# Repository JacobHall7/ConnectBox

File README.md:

# APUConnectBox
Azusa Pacific University Engineering Class of 2019 Senior Design Project

This is a change to the readme file. And another change.

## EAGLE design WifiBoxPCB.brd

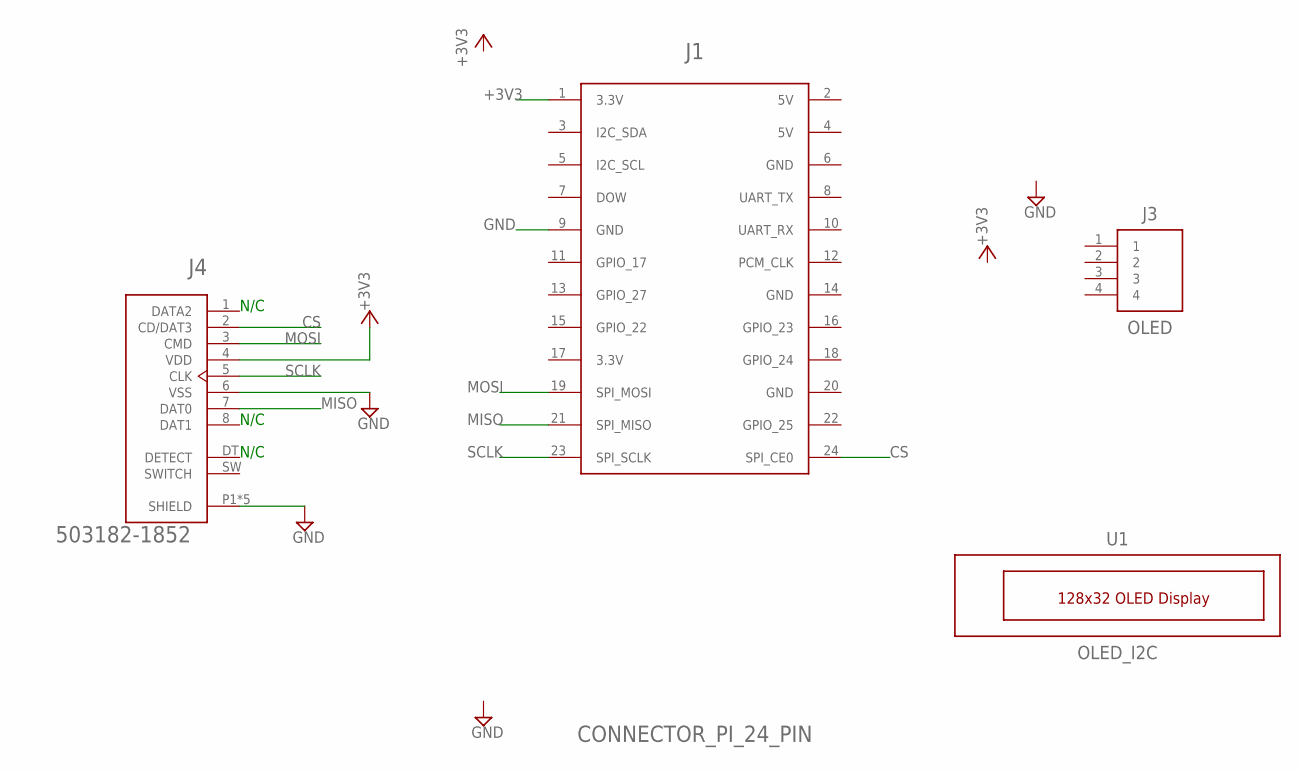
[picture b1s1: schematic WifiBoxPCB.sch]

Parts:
J1: CONNECTOR_PI_24_PIN; 2X12
J3: OLED; ESQ-104-XX-X-S
J4: 503182-1852; MOLEX_503182-1852
U1: OLED_I2C; OLED-I2C

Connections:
+3V3: J1.1 (3.3V), J4.4 (VDD)
CS: J1.24 (SPI_CE0), J4.2 (CD/DAT3)
GND: J1.9 (GND), J4.6 (VSS), J4.P1 (SHIELD), J4.P2 (SHIELD), J4.P3 (SHIELD), J4.P4 (SHIELD), J4.P5 (SHIELD)
MISO: J1.21 (SPI_MISO), J4.7 (DAT0)
MOSI: J1.19 (SPI_MOSI), J4.3 (CMD)
SCLK: J1.23 (SPI_SCLK), J4.5 (CLK)

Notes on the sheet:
N/C

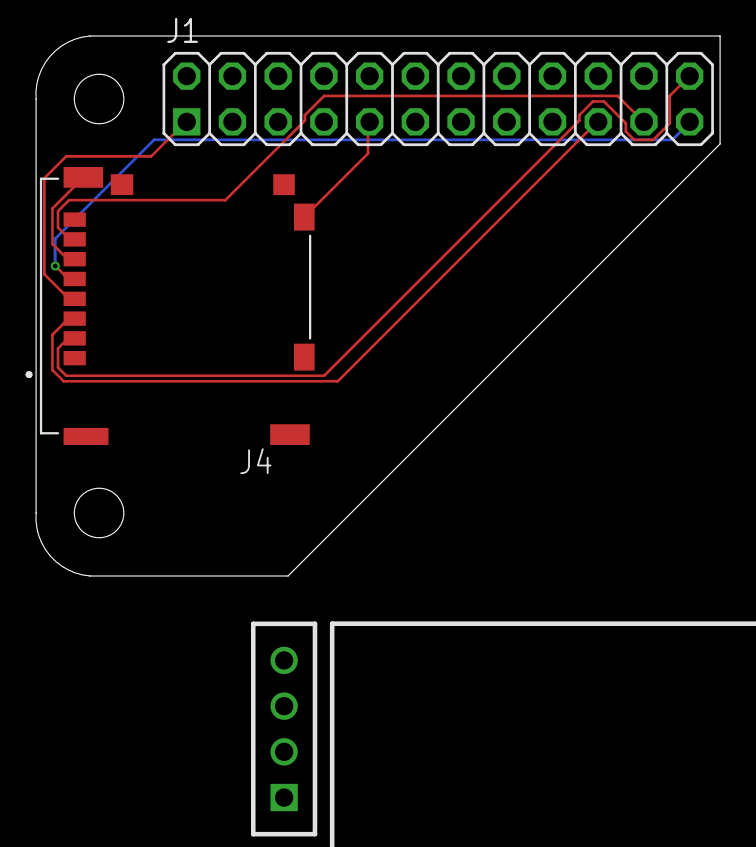
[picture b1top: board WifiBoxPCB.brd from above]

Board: 2 copper layers, 38.0 x 30.0 mm, 4 parts (0 on the bottom side), 6 nets.

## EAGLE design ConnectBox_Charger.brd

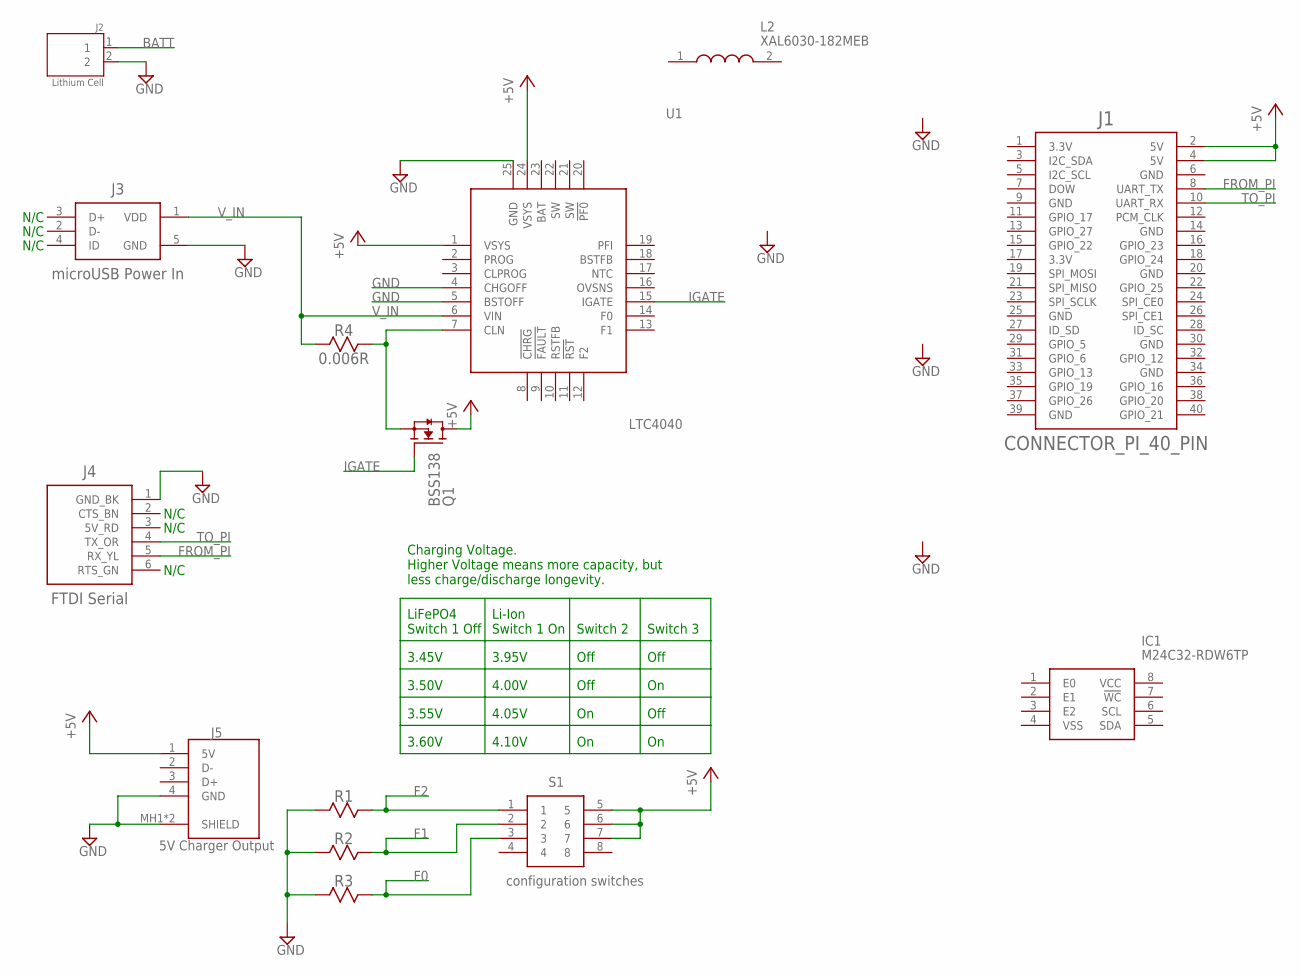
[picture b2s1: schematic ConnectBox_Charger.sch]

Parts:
IC1: M24C32-RDW6TP; SOP65P640X120-8N
J1: CONNECTOR_PI_40_PIN; 2X20
J2: Lithium Cell; JST_S2B-PH-SM4-TB(LF)(SN)
J3: microUSB Power In; FRAMATOME_10118194-0001LF
J4: FTDI Serial; ESQ-106-XX-X-S
J5: 5V Charger Output; SS52100001
L2: XAL6030-182MEB; XAL6030182MEB
Q1: BSS138
R1, R2, R3: RESISTOR0603; RESC1608X55L25N
R4: 0.006R; RESC1608X55L25N
S1: configuration switches; 219-4LPST
U1: LTC4040; QFN50P500X400X80-25N

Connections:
+5V: J1.2 (5V), J1.4 (5V), J5.1 (5V), Q1.D, S1.5, S1.6, S1.7, U1.1 (VSYS), U1.24 (VSYS)
BATT: J2.1
F0: R3.2, S1.3
F1: R2.2, S1.2
F2: R1.2, S1.1
FROM_PI: J1.8 (UART_TX), J4.5 (RX_YL)
GND: J2.2, J3.5 (GND), J4.1 (GND_BK), J5.4 (GND), J5.MH1 (SHIELD), J5.MH2 (SHIELD), R1.1, R2.1, R3.1, U1.4 (CHGOFF), U1.5 (BSTOFF), U1.25 (GND)
IGATE: Q1.G, U1.15 (IGATE)
unnamed: Q1.S, R4.2, U1.7 (CLN)
TO_PI: J1.10 (UART_RX), J4.4 (TX_OR)
V_IN: J3.1 (VDD), R4.1, U1.6 (VIN)

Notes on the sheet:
N/C
Li-Ion Switch 1 On
Switch 3
LiFePO4 Switch 1 Off
Off
Switch 2
3.45V
3.95V
3.50V
4.00V
3.55V
4.05V
3.60V
4.10V
Charging Voltage. Higher Voltage means more capacity, but less charge/discharge longevity.

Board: 2 copper layers, 14 parts (0 on the bottom side), 10 nets, no tracks yet.

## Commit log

2019-02-04 change the README file
    demonstrating a commit.
2019-02-05 testing move of J1#
2019-02-05 edited the readme a second time.
2019-02-19 reset board and schematic down to just the micro SD
2019-02-20 Add frame, +5V, +3.3V, GND, 2x20 connector customized for Raspberry Pi, customized MicroSD devices to library, change Schematic to use parts from ConnectBox Library, start to wire MicroSD socket to P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
2019-02-25 add connector and 128x32 I2C OLED Display.
2019-02-25 addwq OLED to correct library
2019-02-25 add Connector_4 to correct ConnectBox_2019 library for OLED.
2019-02-25 PCB routed contains microSD and OLED screen
2019-02-26 removed WifiBoxPCB.lbr. we are using ConnectBox_2019.lbr.
2019-02-26 Create 3D_Model_ConnectBox
    connectBox shell 3D model
2019-03-01 update microsd, OLED schematic "value"s.
2019-03-02 Add blank ConnectBox Charger Schematic and Board.
2019-03-02 Add LTC4040 Breakout
    Breakout from an Analog Devices/Linear Technology LTC4040 “2.5A Battery Backup Power Manager” IC. Boost SMPS with 5V out, and buck SMPS to charge lithium cell. Li-Ion selectable 3.95V/4.0V/4.05V/4.1V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
    https://www.analog.com/en/products/ltc4040.html
    https://www.analog.com/media/en/technical-documentation/data-sheets/4040fb.pdf
    Package UFD, QFN 4mm x 5mm. 24 pins plus Exposed Pad. LTC4040EUFD
2019-03-02 Continue Charger Schematic and Library Parts Add USB A Receptacle, microUSB Power in, decide on SMT for JST-2, start to add nets.
2019-03-03 Add parts to library, Schematic. Add LTC4040 IC, inductor, 4x DIP switch, table of settings for Battery Chemistry, charging Voltage.
2019-03-06 Tighten LTC4040 and Pi 40-pin connector Schematic symbols from 0.2" to 0.1" pitch, to save space on the Schematic sheet.
2019-03-06 Update LTC4040 and Pi 40-pin connector to 0.1" pin spacing versions to save space on schematic.
2019-03-06 Start connecting LTC4040 charge control IC.
2019-03-12 attempting to push items by firts adding them
2019-03-18 updated rotation on the LED also replaced SSD card socket to a push push holder
2019-03-18 updating library
2019-04-01 3rd round of updates removing the OLED
